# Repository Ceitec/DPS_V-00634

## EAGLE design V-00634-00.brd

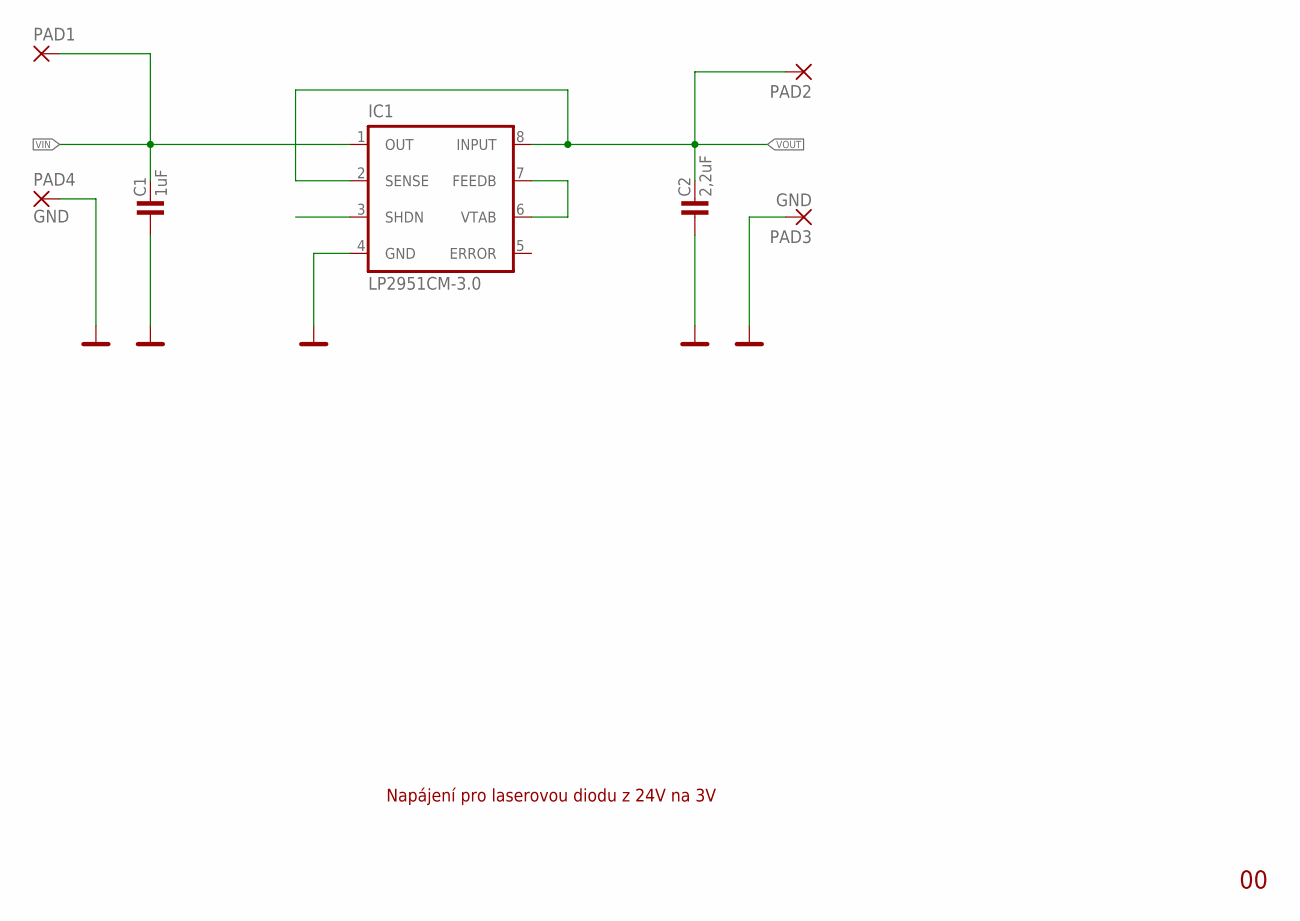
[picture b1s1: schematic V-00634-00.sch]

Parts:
C1: 1uF; 1206
C2: 2,2uF; 1206
IC1: LP2951CM-3.0; SO-08
PAD1, PAD2: 2,54/0,9
PAD3, PAD4: GND; 2,54/0,9

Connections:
GND: C1.1, C2.1, IC1.4 (GND), PAD3.1, PAD4.1
unnamed: IC1.6 (VTAB), IC1.7 (FEEDB)
VIN: C1.2, IC1.1 (OUT), PAD1.1
VOUT: C2.2, IC1.2 (SENSE), IC1.8 (INPUT), PAD2.1

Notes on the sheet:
Napájení pro laserovou diodu z 24V na 3V

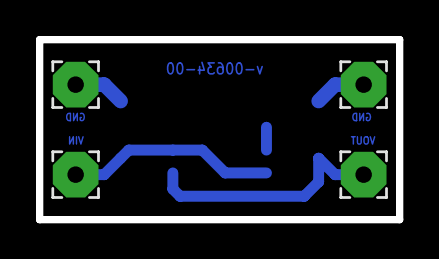
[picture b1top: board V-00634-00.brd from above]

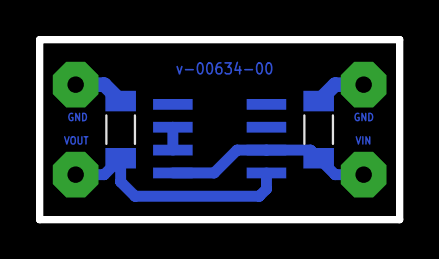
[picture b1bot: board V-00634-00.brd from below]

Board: 2 copper layers, 20.0 x 10.0 mm, 7 parts (3 on the bottom side), 4 nets.

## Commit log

2015-11-10 :space_invader: Added .gitattributes & .gitignore files
2015-11-10 Prvotní verze

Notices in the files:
parts and their libraries:
Copyright (C) PaJa 2001-2014
